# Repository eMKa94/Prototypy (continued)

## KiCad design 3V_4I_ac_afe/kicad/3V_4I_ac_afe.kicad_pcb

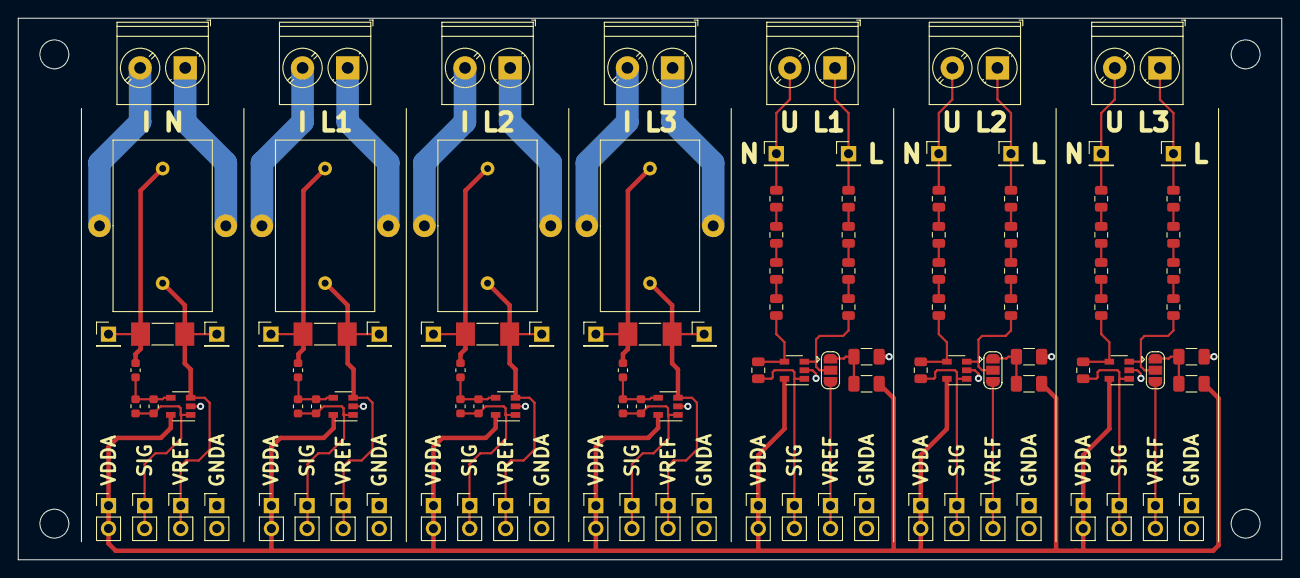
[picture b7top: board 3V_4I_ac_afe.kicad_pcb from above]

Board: 2 copper layers, 140.0 x 60.0 mm, 116 parts (0 on the bottom side), 65 nets.

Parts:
C1, C2, C3, C4: 4,7n; C_0603_1608Metric
CT1, CT2, CT3, CT4: Current_Transformer; CT_talema_pimary_wire
H1, H2, H3, H4: MountingHole; MountingHole_3.2mm_M3
J1, J10, J17, J24, J29, J36, J43: screw; TerminalBlock_Phoenix_PT-1,5-2-5.0-H_1x02_P5.00mm_Horizontal
J2, J3, J30, J31, J37, J38, J44, J45: CT_R; PinHeader_1x01_P2.54mm_Vertical
J4, J11, J18, J25, J32, J39, J46: V_ref; PinHeader_1x02_P2.54mm_Vertical
J5, J12, J19, J26, J33, J40, J47: VDDA; PinHeader_1x02_P2.54mm_Vertical
J6, J13, J20, J27, J34, J41, J48: SIGNAL; PinHeader_1x02_P2.54mm_Vertical
J7, J14, J21, J28, J35, J42, J49: GNDA; PinHeader_1x02_P2.54mm_Vertical
J8, J15, J22: AC L; PinHeader_1x01_P2.54mm_Vertical
J9, J16, J23: AC N; PinHeader_1x01_P2.54mm_Vertical
JP1, JP2, JP3: Jumper_3_Bridged12; SolderJumper-3_P1.3mm_Open_RoundedPad1.0x1.5mm
R1, R37, R40, R43: 10; R_MELF_MMB-0207
R2, R38, R41, R44: 1K; R_0603_1608Metric
R3, R39, R42, R45: 15K; R_0603_1608Metric
R4, R5, R6, R7, R8, R9, R15, R16, R17, R18, R19, R20, R26, R27, R28, R29, R30, R31: 1M; R_0805_2012Metric
R10, R11, R21, R22, R32, R33: 240K; R_0805_2012Metric
R12, R13, R23, R24, R34, R35: R_div_ref; R_1206_3216Metric
R14, R25, R36: 15K; R_0805_2012Metric
U1, U2, U3, U4, U5, U6, U7: MCP6021T; SOT-23-5

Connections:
/ac_i_afe_1/CT_coil: CT1.4, J2.1, R1.2, R2.2
/ac_i_afe_1/ext_ref: CT1.3, J3.1, J4.1, J4.2, R1.1, U1.3
/ac_i_afe_2/CT_coil: CT2.4, J30.1, R37.2, R38.2
/ac_i_afe_2/ext_ref: CT2.3, J31.1, J32.1, J32.2, R37.1, U5.3
/ac_i_afe_3/CT_coil: CT3.4, J37.1, R40.2, R41.2
/ac_i_afe_3/ext_ref: CT3.3, J38.1, J39.1, J39.2, R40.1, U6.3
/ac_i_afe_4/CT_coil: CT4.4, J44.1, R43.2, R44.2
/ac_i_afe_4/ext_ref: CT4.3, J45.1, J46.1, J46.2, R43.1, U7.3
/ac_v_afe_1/AC_V_L: J8.1, J10.1, R4.1
/ac_v_afe_1/AC_V_N: J9.1, J10.2, R5.1
/ac_v_afe_1/Reference_voltage: JP1.2, R10.2, U2.3
/ac_v_afe_1/V_div: JP1.1, R12.1, R13.2
/ac_v_afe_1/ext_ref: J11.1, J11.2, JP1.3
/ac_v_afe_2/AC_V_L: J15.1, J17.1, R15.1
/ac_v_afe_2/AC_V_N: J16.1, J17.2, R16.1
/ac_v_afe_2/Reference_voltage: JP2.2, R21.2, U3.3
/ac_v_afe_2/V_div: JP2.1, R23.1, R24.2
/ac_v_afe_2/ext_ref: J18.1, J18.2, JP2.3
/ac_v_afe_3/AC_V_L: J22.1, J24.1, R26.1
/ac_v_afe_3/AC_V_N: J23.1, J24.2, R27.1
/ac_v_afe_3/Reference_voltage: JP3.2, R32.2, U4.3
/ac_v_afe_3/V_div: JP3.1, R34.1, R35.2
/ac_v_afe_3/ext_ref: J25.1, J25.2, JP3.3
/signal_I1: C1.1, J6.1, J6.2, R3.1, U1.1
/signal_I2: C2.1, J34.1, J34.2, R39.1, U5.1
/signal_I3: C3.1, J41.1, J41.2, R42.1, U6.1
/signal_IN: C4.1, J48.1, J48.2, R45.1, U7.1
/signal_U1: J13.1, J13.2, R14.2, U2.1
/signal_U2: J20.1, J20.2, R25.2, U3.1
/signal_U3: J27.1, J27.2, R36.2, U4.1
GNDA: J7.1, J7.2, J14.1, J14.2, J21.1, J21.2, J28.1, J28.2, J35.1, J35.2, J42.1, J42.2, J49.1, J49.2, R13.1, R24.1, R35.1, U1.2, U2.2, U3.2, U4.2, U5.2, U6.2, U7.2
unnamed: C1.2, R2.1, R3.2, U1.4
unnamed: C2.2, R38.1, R39.2, U5.4
unnamed: C3.2, R41.1, R42.2, U6.4
unnamed: C4.2, R44.1, R45.2, U7.4
unnamed: CT1.1, J1.2
unnamed: CT1.2, J1.1
unnamed: CT2.1, J29.2
unnamed: CT2.2, J29.1
unnamed: CT3.1, J36.2
unnamed: CT3.2, J36.1
unnamed: CT4.1, J43.2
unnamed: CT4.2, J43.1
unnamed: R4.2, R6.1
unnamed: R5.2, R7.1
unnamed: R6.2, R8.1
unnamed: R7.2, R9.1
unnamed: R8.2, R10.1
unnamed: R9.2, R11.1
unnamed: R11.2, R14.1, U2.4
unnamed: R15.2, R17.1
unnamed: R16.2, R18.1
unnamed: R17.2, R19.1
unnamed: R18.2, R20.1
unnamed: R19.2, R21.1
unnamed: R20.2, R22.1
unnamed: R22.2, R25.1, U3.4
unnamed: R26.2, R28.1
unnamed: R27.2, R29.1
unnamed: R28.2, R30.1
unnamed: R29.2, R31.1
unnamed: R30.2, R32.1
unnamed: R31.2, R33.1
unnamed: R33.2, R36.1, U4.4
VDDA: J5.1, J5.2, J12.1, J12.2, J19.1, J19.2, J26.1, J26.2, J33.1, J33.2, J40.1, J40.2, J47.1, J47.2, R12.2, R23.2, R34.2, U1.5, U2.5, U3.5, U4.5, U5.5, U6.5, U7.5

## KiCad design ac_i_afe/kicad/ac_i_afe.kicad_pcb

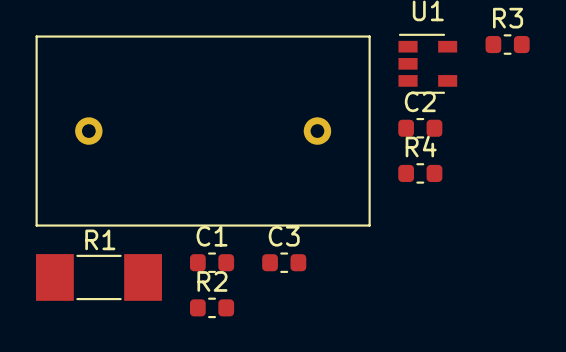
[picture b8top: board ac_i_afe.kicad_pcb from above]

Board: 2 copper layers, 9 parts (0 on the bottom side), 7 nets, no tracks yet.

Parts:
C1: 100n; C_0603_1608Metric
C2, C3: 4,7n; C_0603_1608Metric
CT1: Current_Transformer_prim_free; CT_talema_no_pimary_wire
R1: 10; R_MELF_MMB-0207
R2, R4: 1K; R_0603_1608Metric
R3: 15K; R_0603_1608Metric
U1: MCP6021T; SOT-23-5

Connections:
/Voffset: CT1.1, R1.1, U1.3
/Vout: C3.1, R4.1
/Vsup+: C1.2, U1.5
/Vsup-: C1.1, C3.2, U1.2
unnamed: C2.1, R3.1, R4.2, U1.1
unnamed: C2.2, R2.1, R3.2, U1.4
unnamed: CT1.2, R1.2, R2.2

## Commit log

2020-11-05 AV Voltage analog front end prototype
2020-11-06 Dodany prototyp I AFE oraz 3ph AFE
2020-11-12 dodane prototypy
2020-12-14 added few prototypes and script for zipping kicad gerbers
